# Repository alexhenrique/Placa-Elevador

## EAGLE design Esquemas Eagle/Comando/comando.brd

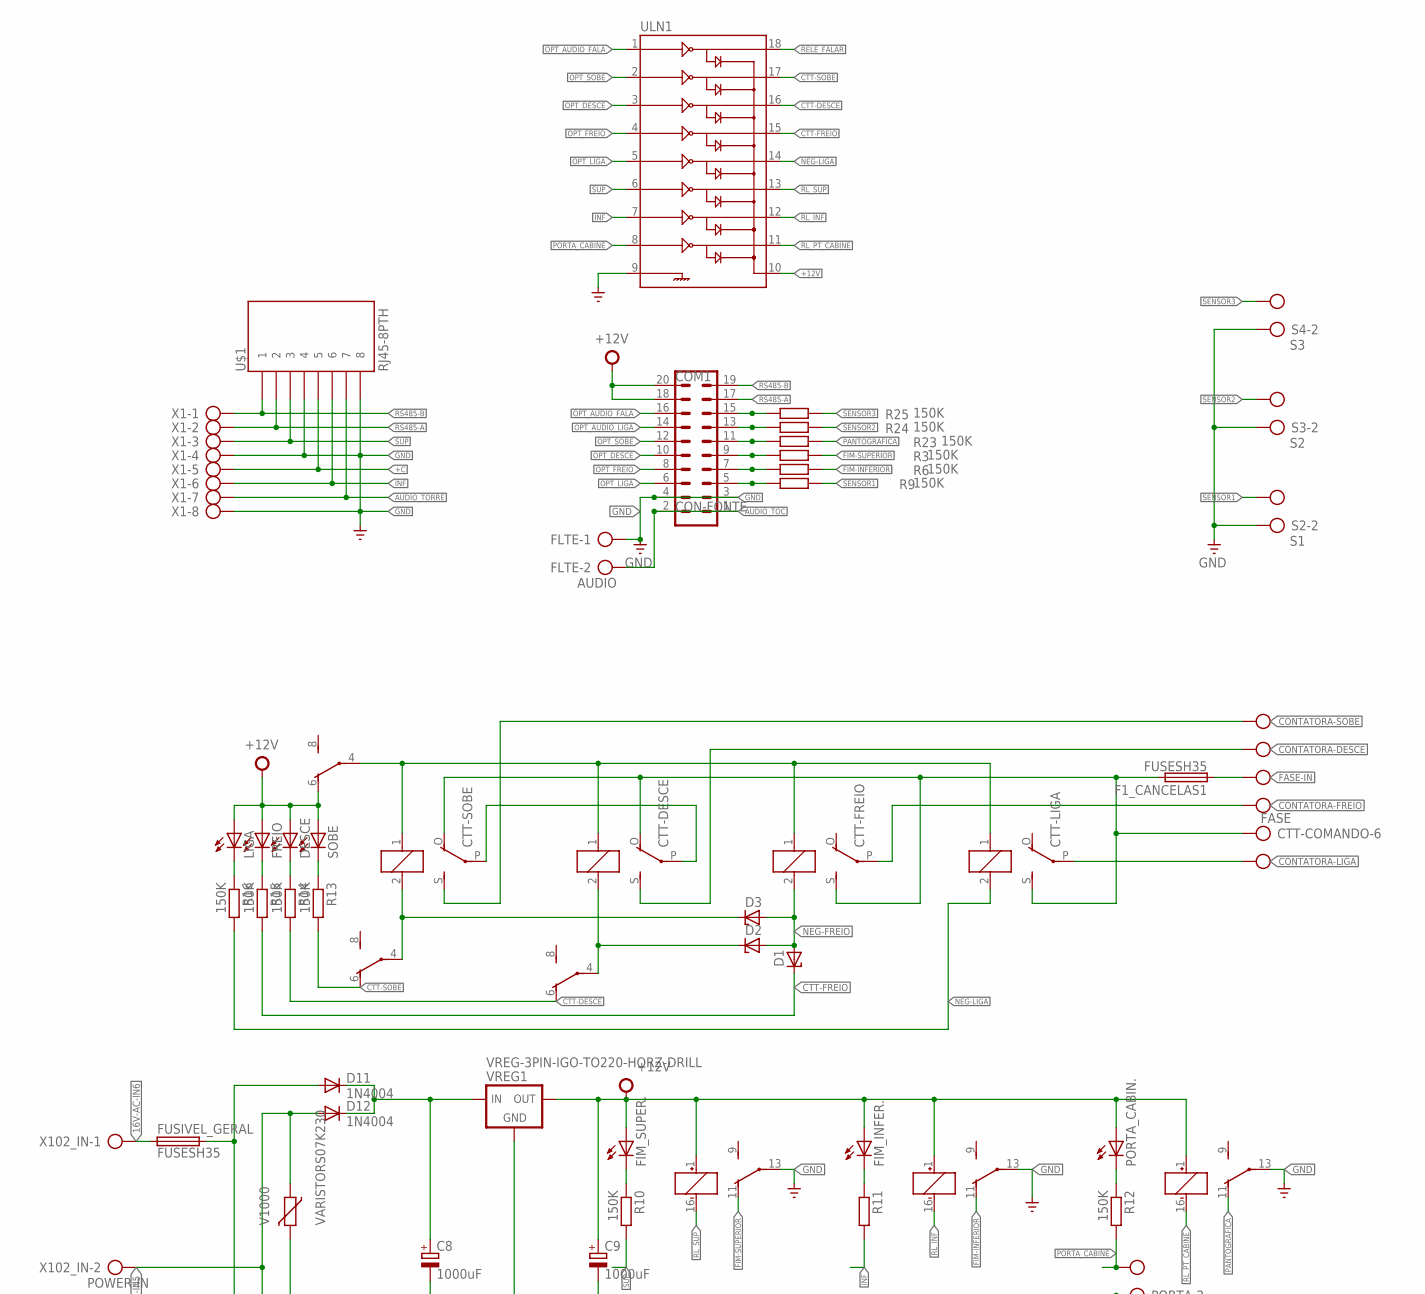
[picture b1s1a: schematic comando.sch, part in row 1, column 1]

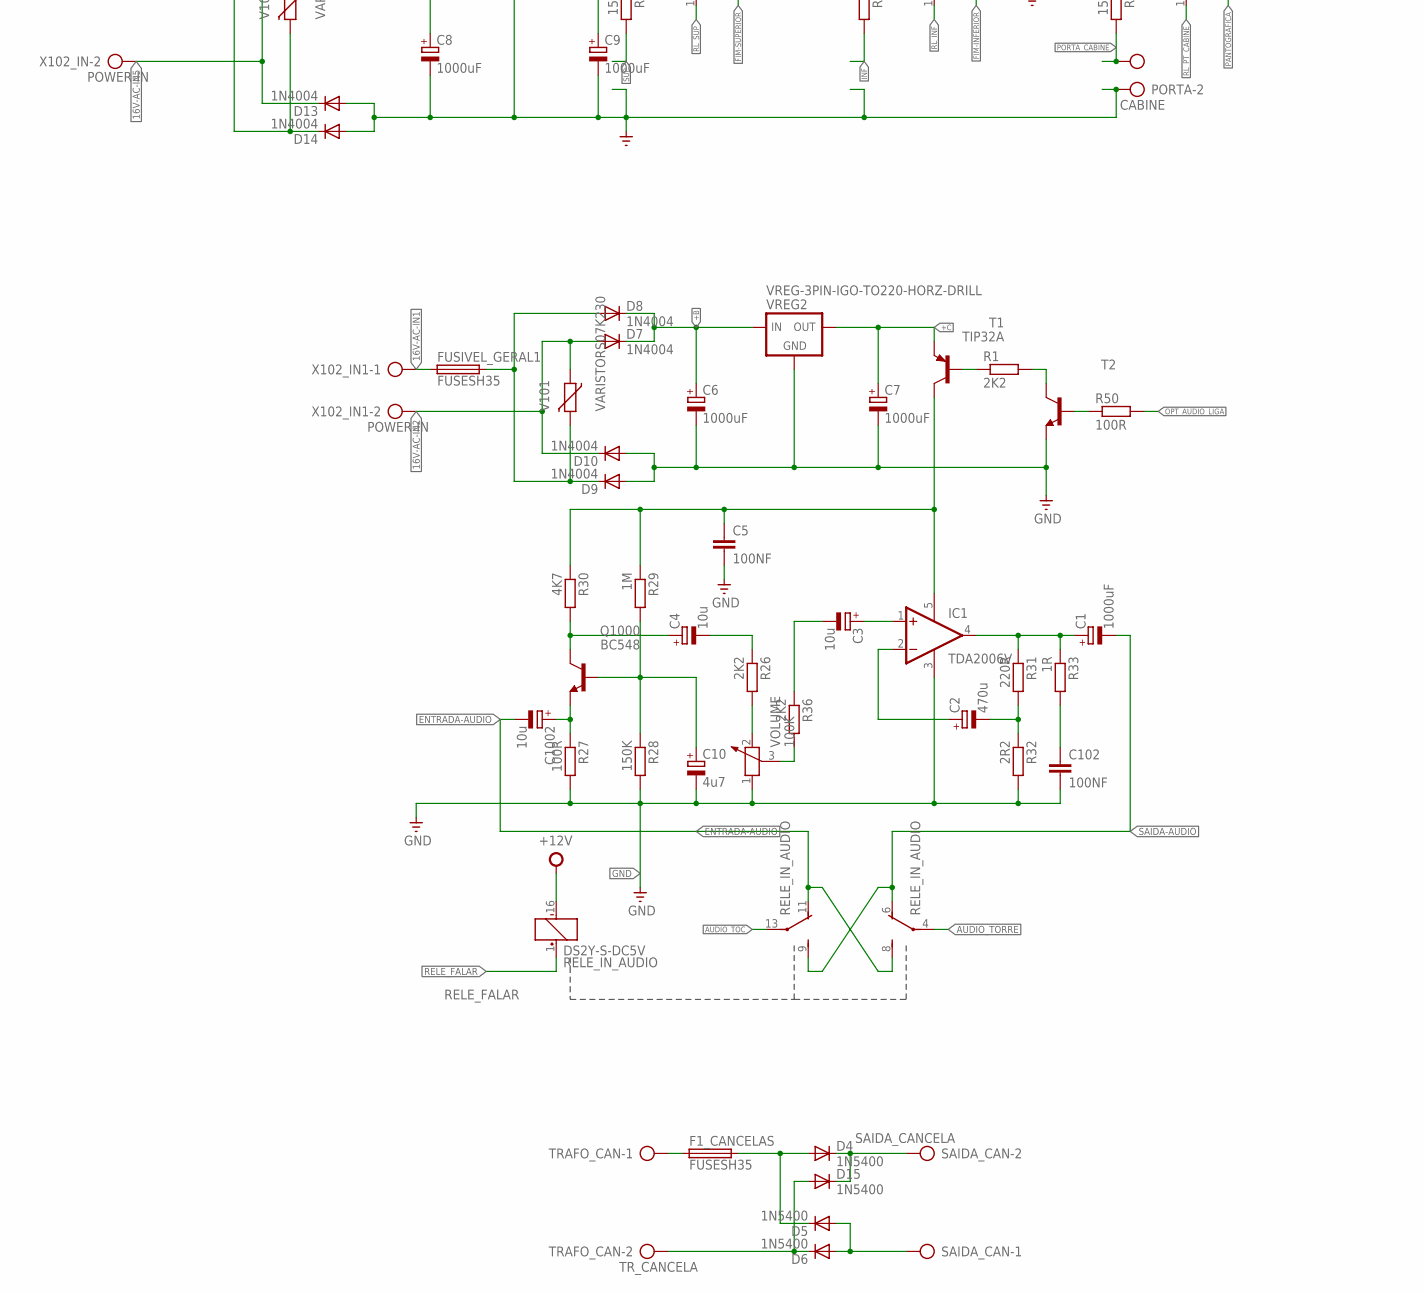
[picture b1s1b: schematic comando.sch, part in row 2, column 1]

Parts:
C1, C6, C7, C8, C9: 1000uF; TAP5-80
C2: 470u; TAP5-80
C3, C4, C1002: 10u; TAP5-45
C5, C102: 100NF; C050-030X075
C10: 4u7; TAP5-45
COM1: CON-FONTE; ML20
CTT-COMANDO: FASE; AK500/6
CTT-DESCE: G5L; G5LE
CTT-FREIO: G5L; G5LE
CTT-LIGA: G5L; G5LE
CTT-SOBE: G5L; G5LE
D1, D2, D3: ZENER-DIODEZD-7.5; ZDIO-7.5
D4, D5, D6, D15: 1N5400; DO201-15
D7, D8, D9, D10, D11, D12, D13, D14: 1N4004; DO41-10
DESCE: LED5MM
F1_CANCELAS, F1_CANCELAS1: FUSESH35; SH25
FIM_INFER.: LED5MM
FIM_SUPER.: LED5MM
FLTE: AUDIO; AK500/2
FREIO: LED5MM
FUSIVEL_GERAL, FUSIVEL_GERAL1: FUSESH35; SH25
IC1: TDA2006V; CB360
LIGA: LED5MM
PORTA: CABINE; AK500/2
PORTA_CABIN.: LED5MM
PORTA_CABINE: DS2Y-S-DC5V; DS2Y
Q1000: BC548; TO92-EBC
R1, R26, R36: 2K2; 0207/10
R3, R6, R9, R10, R11, R12, R13, R14, R15, R16, R23, R24, R25, R28: 150K; 0207/10
R27, R50: 100R; 0207/10
R29: 1M; 0207/10
R30: 4K7; 0207/10
R31: 220R; 0207/10
R32: 2R2; 0207/10
R33: 1R; 0207/10
RELE_IN_AUDIO: DS2Y-S-DC5V; DS2Y
RL_FIM_INFERIOR: DS2Y-S-DC5V; DS2Y
RL_FIM_SUPERIOR: DS2Y-S-DC5V; DS2Y
S2: S1; AK500/2
S3: S2; AK500/2
S4: S3; AK500/2
SAIDA_CAN: SAIDA_CANCELA; AK500/2
SOBE: LED5MM
T1: TIP32A; TO220
T2: BC548-NPN-TO92-CBE; TO92-CBE
TRAFO_CAN: TR_CANCELA; AK500/2
U$1: RJ45-8PTH; RJ45-8
ULN1: ULN2803DIP; DIL18
V101, V1000: VARISTORS07K230; S07K230
VOLUME: 100K; PT-10
VREG1, VREG2: VREG-3PIN-IGO-TO220-HORZ-DRILL; TO220-HORZ-DRILL
X1: RS485_CNT; AK500/8
X102_IN, X102_IN1: POWER-IN; AK500/2

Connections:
16V-AC-IN1: FUSIVEL_GERAL1.1, X102_IN1.1
16V-AC-IN2: D7.A, D10.C, V101.1, X102_IN1.2
16V-AC-IN5: D12.A, D13.C, V1000.1, X102_IN.2
16V-AC-IN6: FUSIVEL_GERAL.1, X102_IN.1
+12V: C9.+, COM1.18, COM1.20, DESCE.A, FIM_INFER..A, FIM_SUPER..A, FREIO.A, LIGA.A, PORTA_CABIN..A, PORTA_CABINE.1 (+), PORTA_CABINE.6 (O), RELE_IN_AUDIO.16 (-), RL_FIM_INFERIOR.1 (+), RL_FIM_SUPERIOR.1 (+), SOBE.A, ULN1.10, VREG1.3 (OUT)
+B: C6.+, D7.C, D8.C, VREG2.1 (IN)
+C: C7.+, T1.3 (E), U$1.5, VREG2.3 (OUT), X1.5
AC-ALIM: CTT-COMANDO.6, CTT-DESCE.O, CTT-FREIO.S, CTT-LIGA.S, CTT-SOBE.O, F1_CANCELAS1.2
AUDIO_TOC: COM1.1, COM1.2, FLTE.2, RELE_IN_AUDIO.13
AUDIO_TORRE: RELE_IN_AUDIO.4, U$1.7, X1.7
CONTATORA-DESCE: CTT-COMANDO.4, CTT-DESCE.S
CONTATORA-FREIO: CTT-COMANDO.3, CTT-FREIO.P
CONTATORA-LIGA: CTT-COMANDO.2, CTT-LIGA.P
CONTATORA-SOBE: CTT-COMANDO.5, CTT-SOBE.S
CTT-DESCE: R14.2, RL_FIM_INFERIOR.6 (O), ULN1.16
CTT-FREIO: D1.C, R15.2, ULN1.15
CTT-SOBE: R13.2, RL_FIM_SUPERIOR.6 (O), ULN1.17
ENTRADA-AUDIO: C1002.-, RELE_IN_AUDIO.8 (S), RELE_IN_AUDIO.11 (O)
FASE-IN: CTT-COMANDO.1, F1_CANCELAS1.1
FIM-INFERIOR: R6.2, RL_FIM_INFERIOR.11 (O)
FIM-SUPERIOR: R3.2, RL_FIM_SUPERIOR.11 (O)
GND: C5.2, C6.-, C7.-, C8.-, C9.-, C10.-, C102.2, COM1.3, COM1.4, D9.A, D10.A, D13.A, D14.A, FLTE.1, IC1.3 (V-), PORTA.2, PORTA_CABINE.13, R27.2, R28.2, R32.2, RL_FIM_INFERIOR.13, RL_FIM_SUPERIOR.13, S2.2, S3.2, S4.2, T2.E, U$1.4, U$1.8, ULN1.9, VOLUME.1, VREG1.2 (GND), VREG2.2 (GND), X1.4, X1.8
INF: R11.2, U$1.6, ULN1.7, X1.6
unnamed: D4.C, D15.C, SAIDA_CAN.2
unnamed: D4.A, D5.C, F1_CANCELAS.2
unnamed: D6.C, D15.A, TRAFO_CAN.2
unnamed: D5.A, D6.A, SAIDA_CAN.1
unnamed: CTT-DESCE.1, CTT-FREIO.1, CTT-LIGA.1, CTT-SOBE.1, PORTA_CABINE.4
unnamed: R36.2, VOLUME.3
unnamed: C8.+, D11.C, D12.C, VREG1.1 (IN)
unnamed: FIM_SUPER..K (C), R10.1
unnamed: R26.2, VOLUME.2
unnamed: FIM_INFER..K (C), R11.1
unnamed: R1.1, T1.1 (B)
unnamed: PORTA_CABIN..K (C), R12.1
unnamed: R13.1, SOBE.K (C)
unnamed: DESCE.K (C), R14.1
unnamed: FREIO.K (C), R15.1
unnamed: LIGA.K (C), R16.1
unnamed: R50.1, T2.B
unnamed: F1_CANCELAS.1, TRAFO_CAN.1
unnamed: C1.+, IC1.4 (OUT), R31.1, R33.1
unnamed: C4.-, R26.1
unnamed: C4.+, Q1000.C, R30.2
unnamed: C10.+, Q1000.B, R28.1, R29.2
unnamed: C1002.+, Q1000.E, R27.1
unnamed: C3.-, R36.1
unnamed: C5.1, IC1.5 (V+), R29.1, R30.1, T1.2 (C)
unnamed: C3.+, IC1.1 (+IN)
unnamed: C2.-, R31.2, R32.1
unnamed: C2.+, IC1.2 (-IN)
unnamed: C102.1, R33.2
NEG-DESCE: CTT-DESCE.2, D2.C, RL_FIM_INFERIOR.4
NEG-FREIO: CTT-FREIO.2, D1.A, D2.A, D3.A
NEG-LIGA: CTT-LIGA.2, R16.2, ULN1.14
NEG-SOB: CTT-SOBE.2, D3.C, RL_FIM_SUPERIOR.4
OPT_AUDIO_FALA: COM1.16, ULN1.1
OPT_AUDIO_LIGA: COM1.14, R50.2
OPT_DESCE: COM1.10, ULN1.3
OPT_FIM_INFERIOR: COM1.7, R6.1
OPT_FIM_SUPERIOR: COM1.9, R3.1
OPT_FREIO: COM1.8, ULN1.4
OPT_LIGA: COM1.6, ULN1.5
OPT_PANTOGRAFICA: COM1.11, R23.1
OPT_SENSOR1: COM1.5, R9.1
OPT_SENSOR2: COM1.13, R24.1
OPT_SENSOR3: COM1.15, R25.1
OPT_SOBE: COM1.12, ULN1.2
PANTOGRAFICA: PORTA_CABINE.11 (O), R23.2
PORTA_CABINE: PORTA.1, R12.2, ULN1.8
RELE_FALAR: RELE_IN_AUDIO.1 (+), ULN1.18
RELE_LIGA_AUDIO: R1.2, T2.C
RL_INF: RL_FIM_INFERIOR.16 (-), ULN1.12
RL_PT_CABINE: PORTA_CABINE.16 (-), ULN1.11
RL_SUP: RL_FIM_SUPERIOR.16 (-), ULN1.13
RS485-A: COM1.17, U$1.2, X1.2
RS485-B: COM1.19, U$1.1, X1.1
SAIDA-AUDIO: C1.-, RELE_IN_AUDIO.6 (O), RELE_IN_AUDIO.9 (S)
SAIDA_FUSIVEL: D11.A, D14.C, FUSIVEL_GERAL.2, V1000.2
SAIDA_FUSIVEL1: D8.A, D9.C, FUSIVEL_GERAL1.2, V101.2
SENSOR1: R9.2, S2.1
SENSOR2: R24.2, S3.1
SENSOR3: R25.2, S4.1
SOB-DESC-PROT: CTT-DESCE.P, CTT-SOBE.P
SUP: R10.2, U$1.3, ULN1.6, X1.3

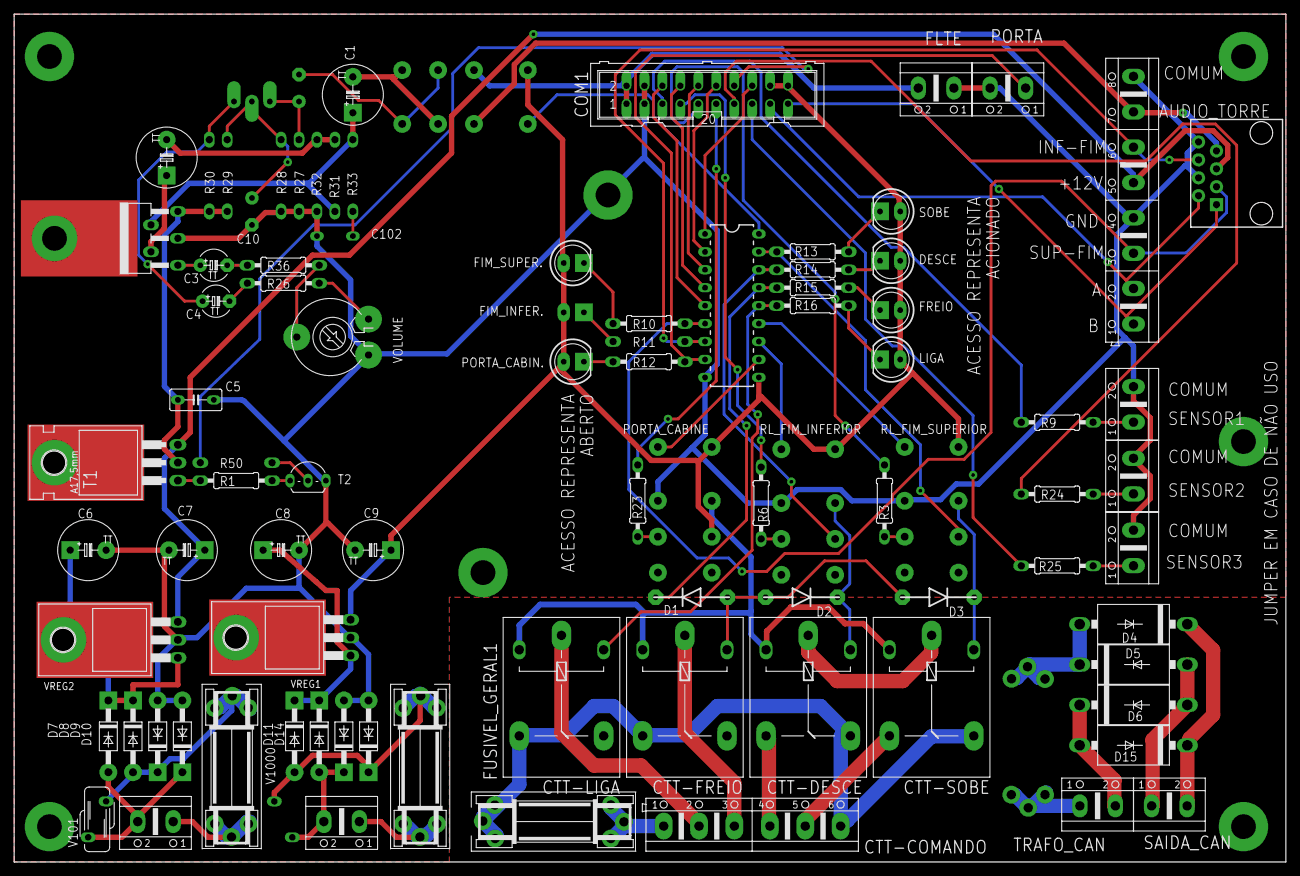
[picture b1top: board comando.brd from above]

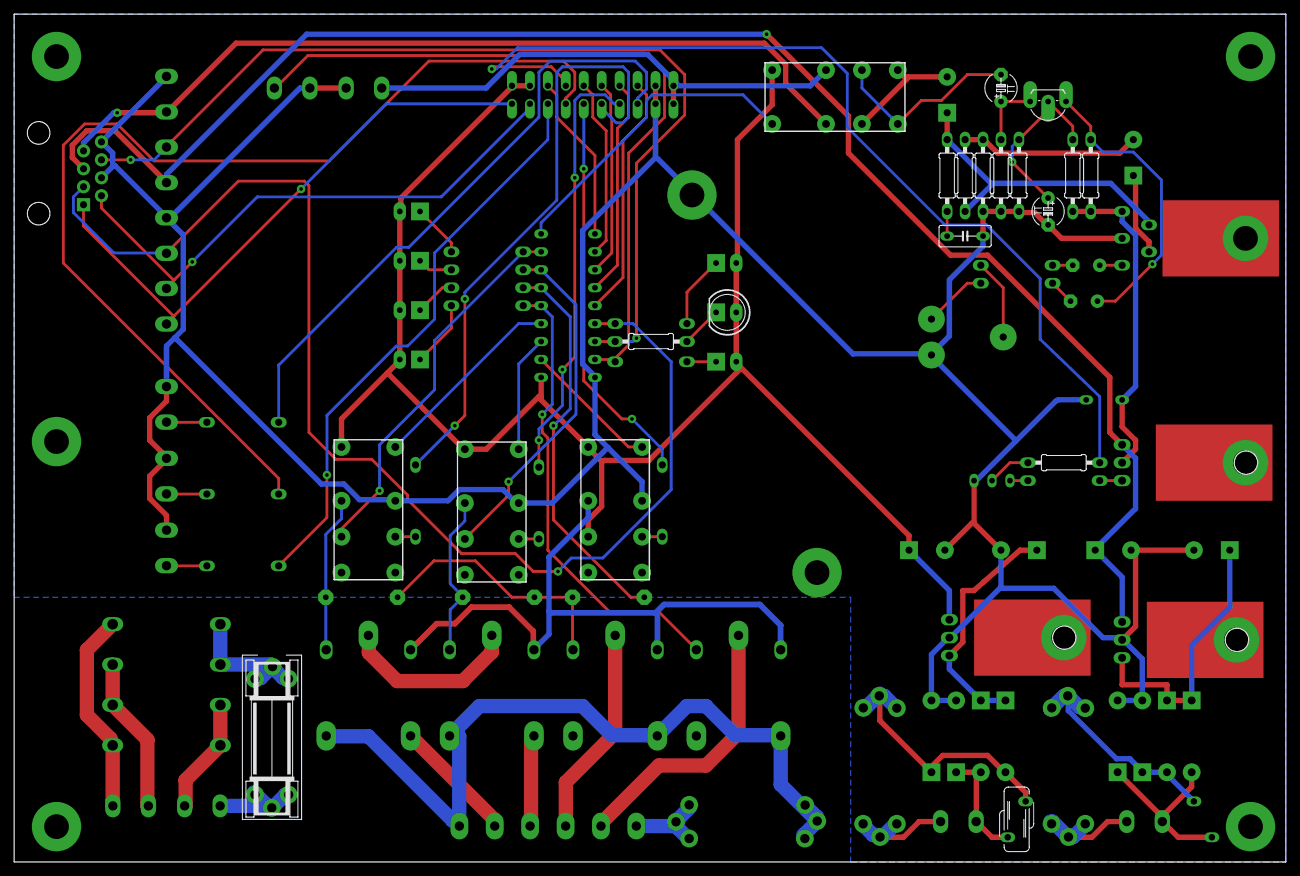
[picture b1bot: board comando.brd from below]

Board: 2 copper layers, 180.0 x 120.0 mm, 93 parts (20 on the bottom side), 85 nets.

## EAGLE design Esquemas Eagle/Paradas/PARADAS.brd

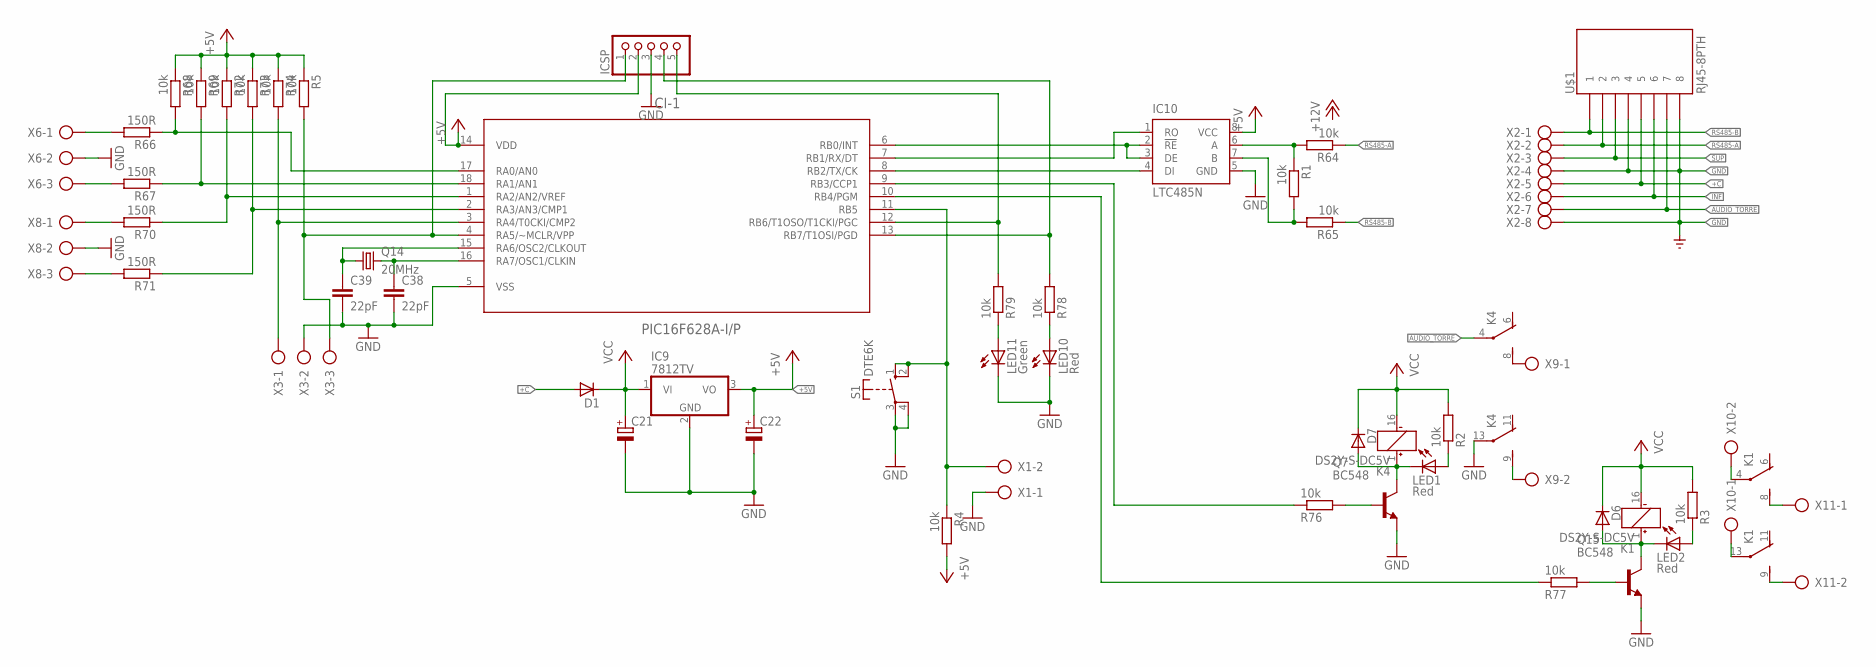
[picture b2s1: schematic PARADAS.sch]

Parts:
C21, C22: CPOL-EUE5-13; E5-13
C38, C39: 22pF; C0805
CI-1: PIC16F628A-I/P; DIP254P762X533-18
D1, D6, D7: BYS10; SOD106A
IC9: 7812TV; TO220V
IC10: LTC485N; DIL08
ICSP: PINHD-1X5; 1X05
K1, K4: DS2Y-S-DC5V; DS2Y
LED1, LED2, LED10: Red; LED5MM
LED11: Green; LED5MM
Q7, Q15: BC548; TO92-EBC
Q14: 20MHz; HC18U-V
R1, R2, R3, R4, R5, R64, R65, R68, R69, R72, R73, R74, R76, R77, R78, R79: 10k; 0207/10
R66, R67, R70, R71: 150R; 0207/10
S1: DTE6K
U$1: RJ45-8PTH; RJ45-8
X1, X9, X10, X11: AK500/2
X2: RS485_CNT; AK500/8
X3, X6, X8: AK500/3

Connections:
+5V: C22.+, CI-1.14 (VDD), IC9.3 (VO), IC10.8 (VCC), ICSP.2, R4.2, R5.1, R68.1, R69.1, R72.1, R73.1, R74.1
+C: D1.A, U$1.5, X2.5
AUDIO_TORRE: K4.4, U$1.7, X2.7
GND: C21.-, C22.-, C38.2, C39.2, CI-1.5 (VSS), IC9.2 (GND), IC10.5 (GND), ICSP.3, K4.13, LED10.K (C), LED11.K (C), Q7.E, Q15.E, S1.3, S1.4, U$1.4, U$1.8, X1.1, X2.4, X2.8, X3.2, X6.2, X8.2
INF: U$1.6, X2.6
unnamed: LED1.A, R2.1
unnamed: IC10.7 (B), R1.2, R65.2
unnamed: IC10.6 (A), R1.1, R64.2
unnamed: LED2.A, R3.1
unnamed: CI-1.11 (RB5), R4.1, S1.1 (S), S1.2 (S), X1.2
unnamed: CI-1.8 (RB2/TX/CK), IC10.4 (DI)
unnamed: K1.4, X10.2
unnamed: CI-1.6 (RB0/INT), IC10.2 (!RE), IC10.3 (DE)
unnamed: K1.13, X10.1
unnamed: CI-1.4 (RA5/~MCLR/VPP), ICSP.1, R5.2, X3.3
unnamed: CI-1.13 (RB7/T1OSI/PGD), ICSP.4, R78.2
unnamed: CI-1.12 (RB6/T1OSO/T1CKI/PGC), ICSP.5, R79.2
unnamed: CI-1.7 (RB1/RX/DT), IC10.1 (RO)
unnamed: C38.1, CI-1.16 (RA7/OSC1/CLKIN), Q14.2
unnamed: C39.1, CI-1.15 (RA6/OSC2/CLKOUT), Q14.1
unnamed: R66.2, X6.1
unnamed: CI-1.17 (RA0/AN0), R66.1, R68.2
unnamed: R67.2, X6.3
unnamed: R70.2, X8.1
unnamed: CI-1.1 (RA2/AN2/VREF), R70.1, R72.2
unnamed: CI-1.18 (RA1/AN1), R67.1, R69.2
unnamed: CI-1.2 (RA3/AN3/CMP1), R71.1, R73.2
unnamed: R71.2, X8.3
unnamed: CI-1.3 (RA4/T0CKI/CMP2), R74.2, X3.1
unnamed: K4.8 (S), X9.1
unnamed: K4.9 (S), X9.2
unnamed: D7.A, K4.1 (+), LED1.K (C), Q7.C
unnamed: Q7.B, R76.2
unnamed: K1.9 (S), X11.2
unnamed: K1.8 (S), X11.1
unnamed: CI-1.9 (RB3/CCP1), R76.1
unnamed: CI-1.10 (RB4/PGM), R77.1
unnamed: D6.A, K1.1 (+), LED2.K (C), Q15.C
unnamed: Q15.B, R77.2
unnamed: LED10.A, R78.1
unnamed: LED11.A, R79.1
RS485-A: R64.1, U$1.2, X2.2
RS485-B: R65.1, U$1.1, X2.1
SUP: U$1.3, X2.3
VCC: C21.+, D1.K, D6.K, D7.K, IC9.1 (VI), K1.16 (-), K4.16 (-), R2.2, R3.2

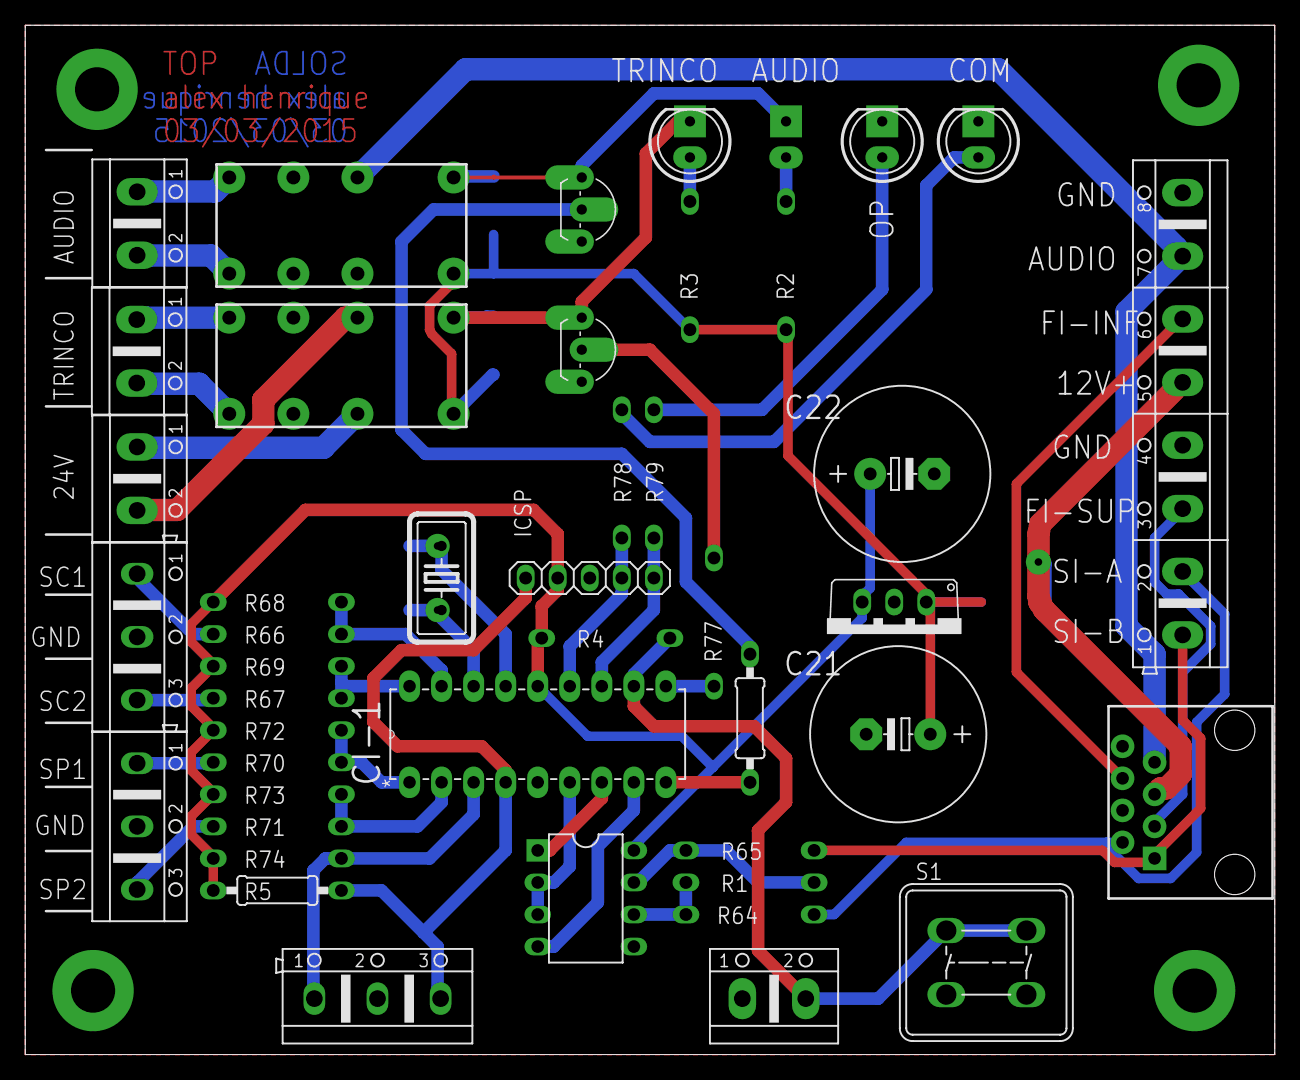
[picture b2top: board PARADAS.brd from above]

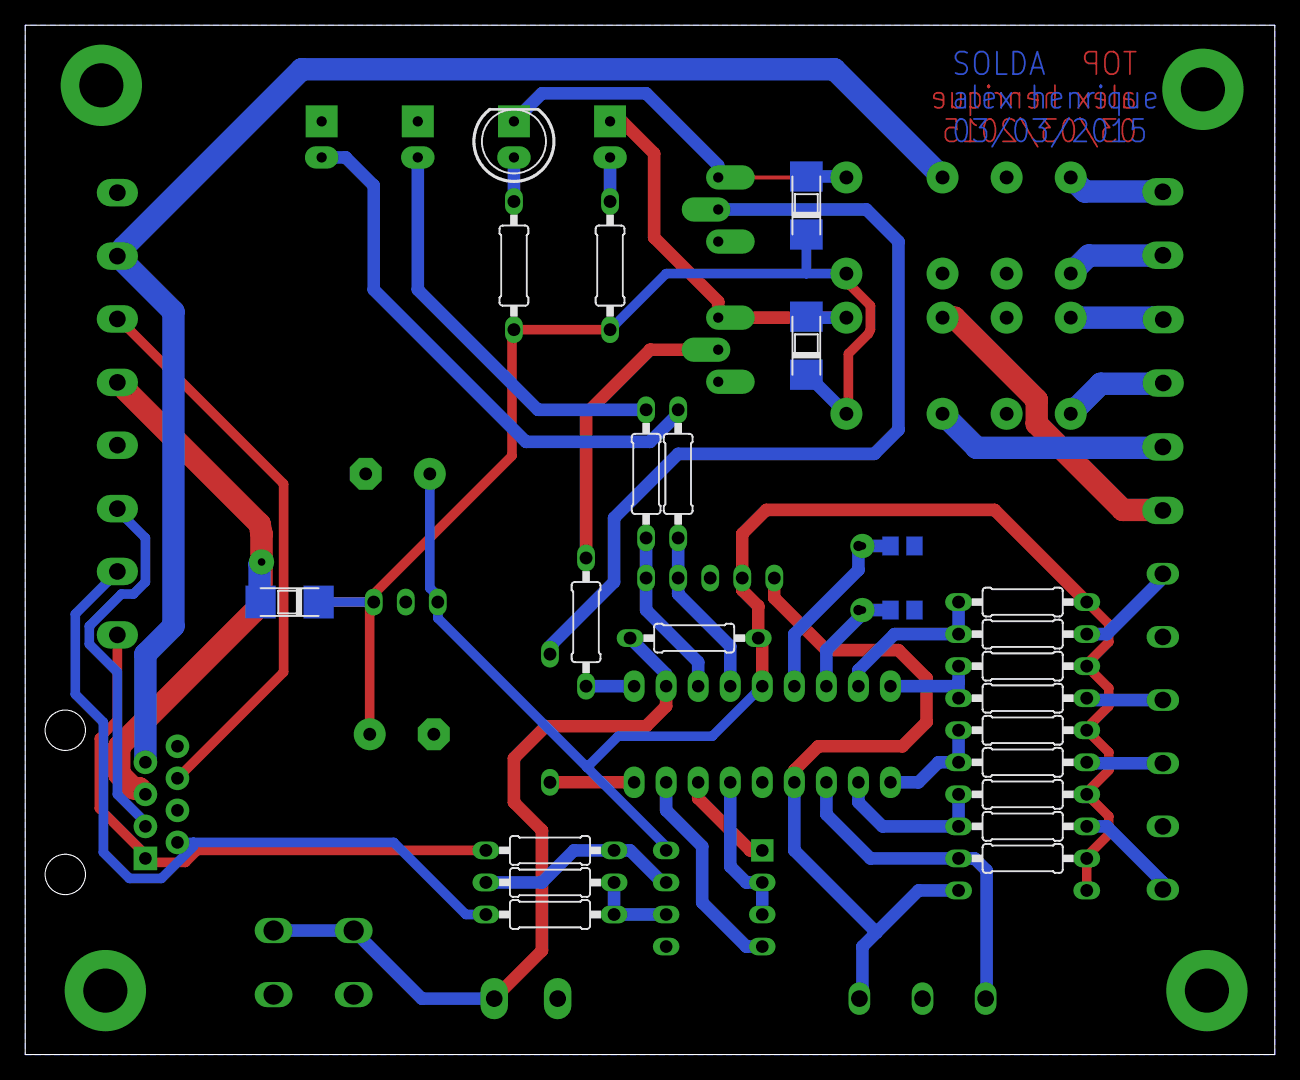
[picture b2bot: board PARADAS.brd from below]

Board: 2 copper layers, 99.0 x 81.6 mm, 50 parts (24 on the bottom side), 45 nets.

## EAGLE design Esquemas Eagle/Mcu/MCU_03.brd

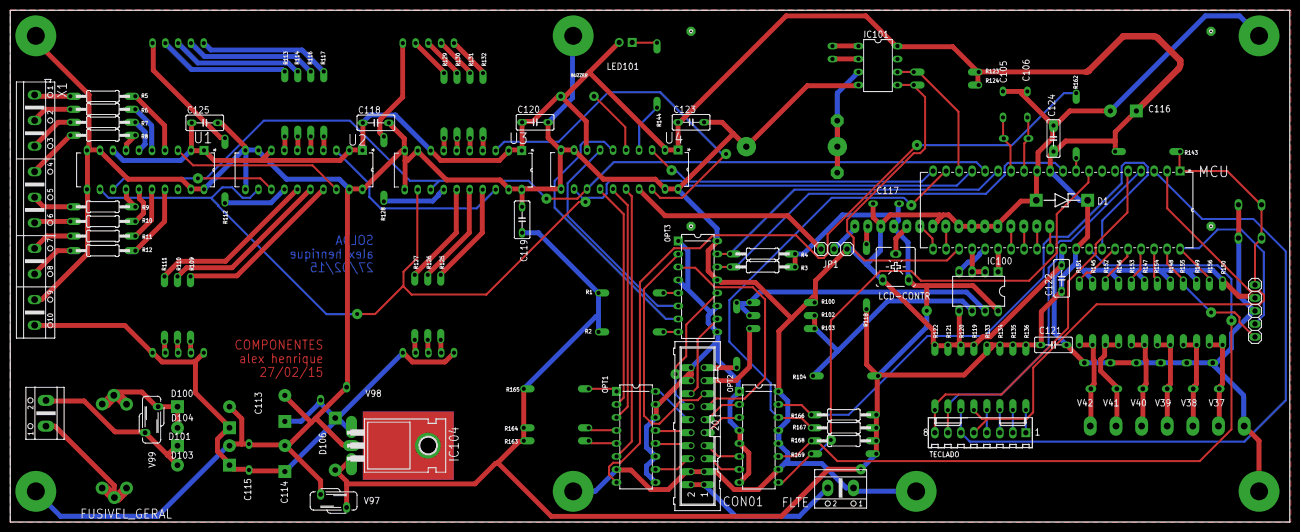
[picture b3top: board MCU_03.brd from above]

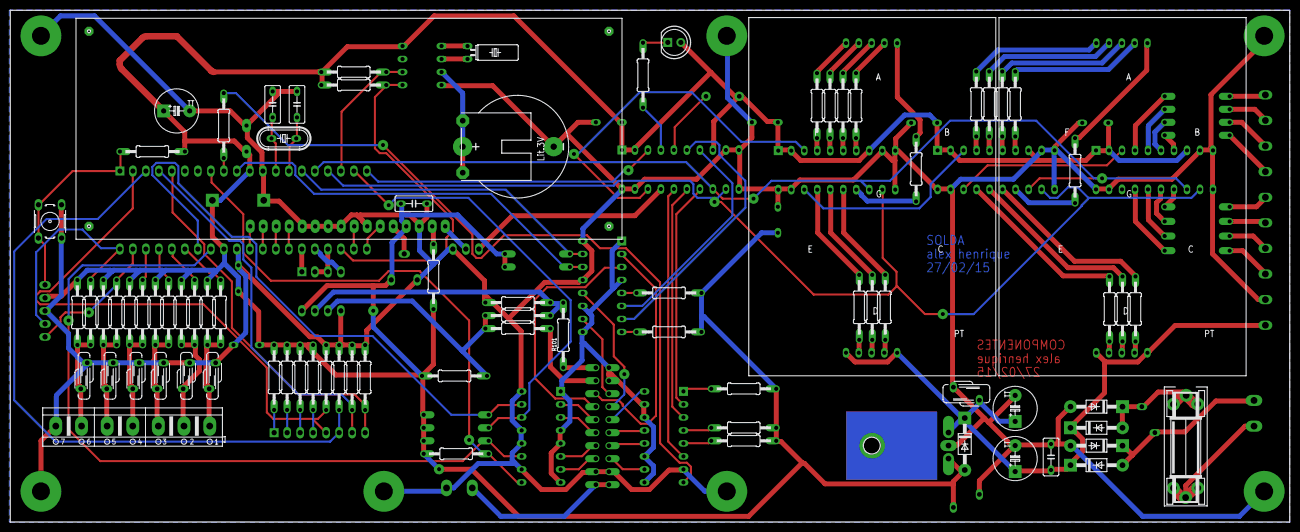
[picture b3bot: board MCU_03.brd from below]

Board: 2 copper layers, 250.0 x 100.0 mm, 126 parts (83 on the bottom side), 140 nets.

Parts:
BUZZER: BUZZERPTH-NS-KIT; BUZZER-12MM-NS-KIT
C105, C106: 22PF; C050-030X075
C113, C114, C116: 1000uF; TAP5-80
C115, C117, C118, C119, C120, C121, C122, C123, C125: 100NF; C050-030X075
C124: 100NF; C050-025X075
CON01: CON-FONTE; ML20
D1: ZENER-5V; ZDIO12.5
D100, D101, D103, D104, D106: 1N4004; DO41-10
FLTE: AUDIO; AK500/2
FUSIVEL_GERAL: FUSESH35; SH25
G100: CR2032H
IC100: LTC485N; DIL08
IC101: DS1307; DIL08
IC104: 7805T; TO220H
JP1: 1X03
JP100: ICSP; 1X05
LCD-CONTR: 10K; CA6V
LED101: HEART_BEAT; LED-5MM
MCU: PIC18F4525; DIP254P1524X635-40
OPT1, OPT2, OPT3: OPTOCOUPLER-CNY74-4H-DIP16; DIL16-3
Q100: 32.768kHZ; TC38H
Q101: 20MHZ; HC49/S
R1, R2, R151, R152, R153, R154, R155, R156, R162, R163, R164, R165: 1K; 0207/12
R3, R4, R166, R167, R168, R169: 4K7; 0207/12
R5, R6, R7, R8, R9, R10, R11, R12, R109, R110, R111, R112, R113, R114, R116, R117, R125, R126, R127, R128, R129, R130, R131, R132: 470R; 0207/12
R100, R101, R102, R103, R104: 10k; 0207/12
R118: 22R; 0207/12
R119, R120, R121, R122, R145, R146, R147, R148, R149, R150: 12K; 0207/12
R123, R124, R144: 2K2; 0207/12
R133: 47K; 0207/12
R134: 18K; 0207/12
R135: 8K; 0207/12
R136: 3K; 0207/12
R143: 10K; 0207/12
S100: RESET; B3F-10XX
TECLADO: 22-27-2081-08; 6410-08
U1, U2, U3, U4: TPIC6B595N; DIP254P762X508-20
U$101, U$103: 2.3"DISPLAY_7_SEG; 2.3"SINGLE_DIGIT_DISPLAY
U$102: 2X16LCDTOP
V37, V38, V39, V40, V41, V42: VARISTORS07K11; S07K11
V97, V98, V99: VARISTORS07K230; S07K230
X1: AK500/10
X101: TECLAS-OP; AK500/7
X102_IN: POWER-IN; AK500/2

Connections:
16V-AC-IN1: FUSIVEL_GERAL.1, X102_IN.1
16V-AC-IN2: D101.C, D103.A, V99.1, X102_IN.2
+5V: BUZZER.+, C116.+, C117.1, C118.1, C119.1, C120.1, C121.1, C122.1, C123.1, C124.1, C125.1, D1.C, D106.A, IC100.8, IC101.8, IC104.3, JP100.2, LCD-CONTR.E, LED101.A, MCU.11, MCU.32, R1.2, R2.2, R3.1, R4.1, R104.2, R118.1, R123.1, R124.2, R133.2, R134.2, R135.2, R136.2, R143.1, R145.1, R146.1, R147.1, R148.1, R149.1, R150.1, R163.2, R164.2, R165.2, R166.1, R167.1, R168.1, R169.1, U1.1, U1.2, U1.8, U2.1, U2.2, U2.8, U3.1, U3.2, U3.8, U4.1, U4.2, U4.8, U$102.2, V97.1
+12V: C113.+, C114.+, C115.1, D103.C, D104.C, D106.C, IC104.1, U$101.COM, U$101.NC, U$103.COM, U$103.NC, V98.1, X1.10
AUDIO: CON01.1, CON01.2, FLTE.2
AVDD: CON01.18, CON01.20, OPT1.9, OPT1.11, OPT1.14, OPT1.15, OPT2.1, OPT2.4, OPT2.5, OPT2.8, OPT3.1, OPT3.4, OPT3.9, OPT3.11
CMD-AUDIO: R148.2, R154.2, V39.2, X101.4
CMD-DESCE: R147.2, R153.2, V40.2, X101.3
CMD-NIVELA: R149.2, R155.2, V38.2, X101.5
CMD-PARA: R146.2, R152.2, V41.2, X101.2
CMD-SOBE: R145.2, R151.2, V42.2, X101.1
CTT_DESCE: OPT1.3, U4.15
CTT_FREIO: OPT1.6, U4.16
CTT_SOBE: OPT1.2, U4.14
D1-A: R129.2, U$103.A
D1-B: R128.2, U$103.B
D1-C: R127.2, U$103.C
D1-D: R126.2, U$103.D
D1-E: R125.2, U$103.E
D1-F: R131.2, U$103.F
D1-G: R132.2, U$103.G
D1-PT: R130.2, U$103.PT
D2-A: R113.2, U$101.A
D2-B: R112.2, U$101.B
D2-C: R111.2, U$101.C
D2-D: R110.2, U$101.D
D2-E: R109.2, U$101.E
D2-F: R116.2, U$101.F
D2-G: R117.2, U$101.G
D2-PT: R114.2, U$101.PT
GND: C105.2, C106.2, C113.-, C114.-, C115.2, C116.-, C117.2, C118.2, C119.2, C120.2, C121.2, C122.2, C123.2, C124.2, C125.2, CON01.3, CON01.4, D1.A, D100.A, D101.A, FLTE.1, G100.-, IC100.5, IC101.4, IC104.2, JP1.3, JP100.3, LCD-CONTR.A, MCU.12, MCU.31, OPT1.7, OPT2.10, OPT2.12, OPT2.13, OPT2.16, OPT3.13, OPT3.16, R100.1, R119.1, R120.1, R121.1, R122.1, S100.1, S100.2, U1.9, U1.10, U1.11, U1.19, U1.20, U2.9, U2.10, U2.11, U2.19, U2.20, U3.9, U3.10, U3.11, U3.19, U3.20, U4.9, U4.10, U4.11, U4.19, U4.20, U$102.1, U$102.5, U$102.7, U$102.8, U$102.9, U$102.10, V37.1, V38.1, V39.1, V40.1, V41.1, V42.1, V97.2, V98.2, X1.9, X101.7
IR-ATE: R150.2, R156.2, V37.2, X101.6
LCD_BLK: JP1.2, U$102.16
LCD_NEG: JP1.1, U4.17
MAX485-A: IC100.6, R102.1, R103.2, R104.1
MAX485-B: IC100.7, R100.2, R101.2, R102.2
MCLR: JP100.1, MCU.1, R143.2, S100.3, S100.4
unnamed: LED101.K, R144.2
unnamed: U2.3, U3.18
unnamed: R118.2, U$102.15
unnamed: R117.1, U2.4
unnamed: R116.1, U2.5
unnamed: R114.1, U2.6
unnamed: R113.1, U2.7
unnamed: IC101.1, Q100.1
unnamed: IC101.2, Q100.2
unnamed: R112.1, U2.14
unnamed: R111.1, U2.15
unnamed: R110.1, U2.16
unnamed: R109.1, U2.17
unnamed: R133.1, TECLADO.4
unnamed: U3.3, U4.18
unnamed: OPT3.6, U4.7
unnamed: R132.1, U3.4
unnamed: R131.1, U3.5
unnamed: R130.1, U3.6
unnamed: R129.1, U3.7
unnamed: R128.1, U3.14
unnamed: R127.1, U3.15
unnamed: R126.1, U3.16
unnamed: R125.1, U3.17
unnamed: OPT3.7, U4.6
unnamed: OPT3.5, R1.1
unnamed: OPT3.8, R2.1
unnamed: R144.1, U4.4
unnamed: R134.1, TECLADO.3
unnamed: R135.1, TECLADO.2
unnamed: R136.1, TECLADO.1
unnamed: BUZZER.-, U4.5
unnamed: CON01.13, OPT3.3
unnamed: CON01.15, OPT3.2
unnamed: OPT1.1, R165.1
unnamed: OPT1.4, R164.1
unnamed: OPT1.5, R163.1
unnamed: OPT1.8, R162.1
unnamed: U1.3, U2.18
unnamed: R5.1, U1.4
unnamed: R6.1, U1.5
unnamed: R7.1, U1.6
unnamed: R8.1, U1.7
unnamed: R9.1, U1.14
unnamed: R10.1, U1.15
unnamed: R11.1, U1.16
unnamed: R12.1, U1.17
unnamed: R5.2, X1.1
unnamed: R6.2, X1.2
unnamed: R7.2, X1.3
unnamed: R8.2, X1.4
unnamed: R9.2, X1.5
unnamed: R10.2, X1.6
unnamed: R11.2, X1.7
unnamed: R12.2, X1.8
OPT_AUDIO_FALA: CON01.16, OPT3.10
OPT_AUDIO_LIGA: CON01.14, OPT3.12
OPT_DESCE: CON01.10, OPT1.13
OPT_FIM_INFERIOR: CON01.7, OPT2.6
OPT_FIM_SUPERIOR: CON01.9, OPT2.3
OPT_FREIO: CON01.8, OPT1.12
OPT_LIGA: CON01.6, OPT1.10
OPT_PANTOGRAFICA: CON01.11, OPT2.2
OPT_SENSOR1: CON01.5, OPT2.7
OPT_SOBE: CON01.12, OPT1.16
RA0: MCU.2, R119.2, TECLADO.5
RA1: MCU.3, R120.2, TECLADO.6
RA2: MCU.4, R121.2, TECLADO.7
RA3: MCU.5, R122.2, TECLADO.8
RA6: C105.1, MCU.14, Q101.1
RA7: C106.1, MCU.13, Q101.2
RB0: MCU.33, OPT2.11, R168.2
RB1: MCU.34, OPT2.15, R166.2
RB2: MCU.35, R151.1
RB3: MCU.36, R152.1
RB4: MCU.37, R153.1
RB5: MCU.38, R154.1
RB6: JP100.5, MCU.39, R155.1
RB7: JP100.4, MCU.40, R156.1
RC0: MCU.15, OPT3.15, R4.2
RC1: MCU.16, U1.13, U2.13, U3.13, U4.13
RC2: MCU.17, U1.12, U2.12, U3.12, U4.12
RC3: IC101.6, MCU.18, R123.2
RC4: IC101.5, MCU.23, R124.1
RC5: IC100.2, IC100.3, MCU.24
RC6: IC100.4, MCU.25
RC7: IC100.1, MCU.26
RD0: MCU.19, OPT2.14, R167.2
RD1: MCU.20, U4.3
RD2: MCU.21, U$102.4
RD3: MCU.22, U$102.6
RD4: MCU.27, U$102.11
RD5: MCU.28, U$102.12
RD6: MCU.29, U$102.13
RD7: MCU.30, U$102.14
RE0: MCU.8, OPT2.9, R169.2
RE1: MCU.9, R162.2
RE2: MCU.10, OPT3.14, R3.2
RS485-A: CON01.17, R103.1
RS485-B: CON01.19, R101.1
SAIDA_FUSIVEL: D100.C, D104.A, FUSIVEL_GERAL.2, V99.2
VBAT+: G100.+, IC101.3
VOO: LCD-CONTR.S, U$102.3

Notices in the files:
parts and their libraries:
SparkFun-Connectors: Licensing: CC v3.0 Share-Alike You are welcome to use this library for commercial purposes.
